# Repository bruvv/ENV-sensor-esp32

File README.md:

# ENV Sensor ESP32

Custom ESP32-S3 environmental sensor PCB designed for use with ESPHome and Home Assistant.

The board combines several environmental sensors, a 128×128 OLED display and an HLK-LD2450 mmWave presence sensor on a compact custom PCB.

## Features

- ESP32-S3 DevKitC N16R8
- Sensirion SCD30 CO₂ sensor
- Sensirion SEN55 environmental sensor
- MS5611 barometric pressure sensor
- BH1750 ambient light sensor
- ZJY-M150 128×128 OLED with SSD1327 controller
- HLK-LD2450 mmWave presence sensor
- Shared I²C bus for environmental sensors
- SPI interface for the OLED display
- Hardware UART for the LD2450
- 5 V and 3.3 V power rails
- 4-layer PCB
- 55 × 70 mm board
- Designed in KiCad 10

## Sensors

| Component | Function | Supply | Interface |
| --- | --- | ---: | --- |
| ESP32-S3 DevKitC N16R8 | Main controller, Wi-Fi and Bluetooth | 5 V | - |
| Sensirion SCD30 | CO₂, temperature and humidity | 5 V | I²C |
| Sensirion SEN55 | PM1.0, PM2.5, PM4, PM10, VOC, NOx, temperature and humidity | 5 V | I²C |
| MS5611 | Barometric pressure | 3.3 V | I²C |
| BH1750 | Ambient light | 3.3 V | I²C |
| ZJY-M150 / SSD1327 | 128×128 OLED display | 3.3 V | SPI |
| HLK-LD2450 | mmWave presence and multi-target tracking | 5 V | UART |

## ESP32 Pin Mapping

### I²C

| Signal | ESP32-S3 |
| --- | --- |
| SDA | GPIO8 |
| SCL | GPIO9 |

The environmental sensors share the I²C bus.

| Sensor | I²C address |
| --- | ---: |
| SCD30 | `0x61` |
| SEN55 | `0x69` |
| BH1750 | `0x23` |
| MS5611 | `0x77` |

The PCB contains 4.7 kΩ pull-up resistors for SDA and SCL.

## SSD1327 OLED

The ZJY-M150 OLED is operated in 4-wire SPI mode.

| OLED signal | ESP32-S3 |
| --- | --- |
| CS | GPIO10 |
| MOSI / SDA | GPIO11 |
| CLK / SCL | GPIO12 |
| DC | GPIO13 |
| RESET | GPIO14 |

## HLK-LD2450

The LD2450 uses a dedicated hardware UART.

| Signal | ESP32-S3 |
| --- | --- |
| LD2450 RX | GPIO17 / ESP32 TX |
| LD2450 TX | GPIO18 / ESP32 RX |

UART configuration:

- Baud rate: `256000`
- Data bits: `8`
- Parity: none
- Stop bits: `1`

## PCB

The current PCB revision is designed in KiCad 10.

| Property | Value |
| --- | --- |
| Dimensions | 55 × 70 mm |
| Copper layers | 4 |
| Top copper | `F.Cu` |
| Inner layer 1 | `In1.Cu` |
| Inner layer 2 | `In2.Cu` |
| Bottom copper | `B.Cu` |

The repository contains the KiCad project files as well as production Gerber and drill files.

## LD2450 Connector

The HLK-LD2450 is connected through an 8-pin dual-row SMD female socket.

Required connector specification:

| Property | Requirement |
| --- | --- |
| Type | Female PCB socket |
| Contacts | 8 |
| Rows | 2 × 4 |
| Pitch | 2.00 mm |
| Mounting | SMD / SMT |
| Orientation | Straight |

A suitable branded connector is:

**Würth Elektronik 62100821821**

- 2 × 4
- 8 contacts
- 2.00 mm pitch
- Female
- SMD

For generic alternatives, search for:

`2.0mm 2x4 8 pin female SMD header`

## SEN55 Connection

The SEN55 is mounted away from the main PCB to keep its airflow unobstructed.

The connection provides:

| Signal |
| --- |
| 5 V |
| GND |
| SDA |
| SCL |
| GND / SEL |

## Bill of Materials

| Qty | Component | Notes |
| ---: | --- | --- |
| 1 | ESP32-S3 DevKitC N16R8 | ESP32-S3-WROOM based |
| 1 | Sensirion SCD30 | CO₂ sensor |
| 1 | Sensirion SEN55 | Environmental and particulate sensor |
| 1 | MS5611 module | Pressure sensor |
| 1 | BH1750 module | Ambient light sensor |
| 1 | ZJY-M150 128×128 OLED | SSD1327 controller, 7-pin |
| 1 | HLK-LD2450 | mmWave presence sensor |
| 1 | 2×4 2.00 mm female SMD socket | LD2450 connector |
| 2 | 4.7 kΩ resistor | I²C pull-ups |

## Design Considerations

### SCD30

The SCD30 should be kept away from heat sources and strong direct airflow that could influence its temperature and CO₂ measurements.

Datasheet:  
https://sensirion.com/media/documents/4EAF6AF8/61652C3C/Sensirion_CO2_Sensors_SCD30_Datasheet.pdf

### SEN55

The SEN55 requires unobstructed airflow through its inlet and outlet.

For best performance:

- Keep the inlet and outlet separated.
- Avoid recirculating exhaust air into the inlet.
- Keep the sensor away from heat sources.
- Orient the sensor so dust cannot easily accumulate inside.
- Keep the fan inlet and exhaust unobstructed.

Datasheet:  
https://sensirion.com/media/documents/6791EFA0/62A1F68F/Sensirion_Datasheet_Environmental_Node_SEN5x.pdf

### MS5611

Keep the pressure sensor away from the ESP32 voltage regulator and other heat-producing components.

Datasheet:  
https://www.te.com/commerce/DocumentDelivery/DDEController?Action=showdoc&DocId=Data+Sheet%7FMS5611-01BA03%7FB3%7Fpdf%7FEnglish%7FENG_DS_MS5611-01BA03_B3.pdf%7FCAT-BLPS0036

### BH1750

The BH1750 needs a clear optical path to the room.

Avoid placing it behind opaque enclosure material or in the shadow of other components.

Datasheet:  
https://components101.com/sites/default/files/component_datasheet/BH1750.pdf

### SSD1327 OLED

The display is a ZJY-M150 1.5-inch 128×128 OLED using an SSD1327 controller.

The PCB uses SPI for the display.

SSD1327 datasheet:  
https://www.waveshare.com/w/upload/a/ac/SSD1327-datasheet.pdf

### HLK-LD2450

The LD2450 provides mmWave presence detection and multi-target position tracking.

Placement and enclosure design can significantly affect radar performance.

Recommendations:

- Face the radar toward the room.
- Avoid metal directly in front of the antenna.
- Keep sufficient clearance around the antenna area.
- Avoid placing large copper areas or metal parts directly in the radar field of view.

## Repository Structure

`envsensor/`  
KiCad schematic, PCB project and project-specific libraries.

`gerber/`  
Production Gerber and drill files.

`datasheet/`  
Component documentation.

`docs/`  
Hardware design and implementation documentation.

`README.md`  
Project documentation.

## Manufacturing

The `gerber/` directory contains the generated PCB production files, including:

- `F.Cu`
- `In1.Cu`
- `In2.Cu`
- `B.Cu`
- `F.Mask`
- `B.Mask`
- `F.Paste`
- `B.Paste`
- `F.Silkscreen`
- `B.Silkscreen`
- `Edge.Cuts`
- PTH drill file
- NPTH drill file

The repository also contains `gerber/gerber.zip`, which can be uploaded to most PCB manufacturers.

Always verify the Gerbers in the PCB manufacturer's Gerber viewer before placing an order.

## Software

The board is intended for use with ESPHome and Home Assistant.

Useful ESPHome documentation:

- SCD30: https://esphome.io/components/sensor/scd30/
- SEN5x: https://esphome.io/components/sensor/sen5x/
- BH1750: https://esphome.io/components/sensor/bh1750/
- MS5611: https://esphome.io/components/sensor/ms5611/
- SSD1327: https://esphome.io/components/display/ssd1327/
- LD2450: https://esphome.io/components/sensor/ld2450/

## License

See [LICENSE](LICENSE).

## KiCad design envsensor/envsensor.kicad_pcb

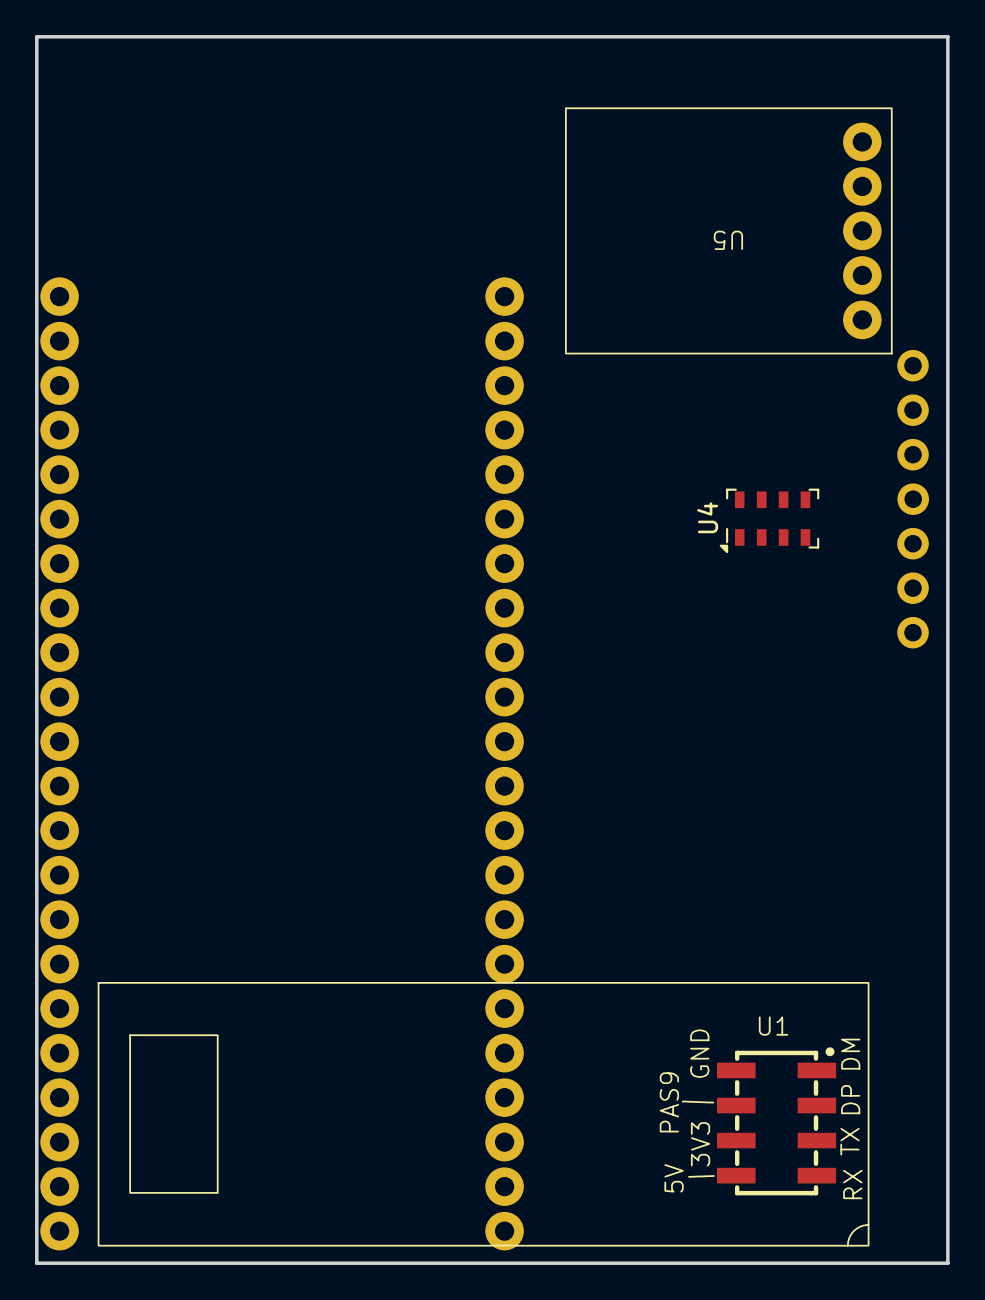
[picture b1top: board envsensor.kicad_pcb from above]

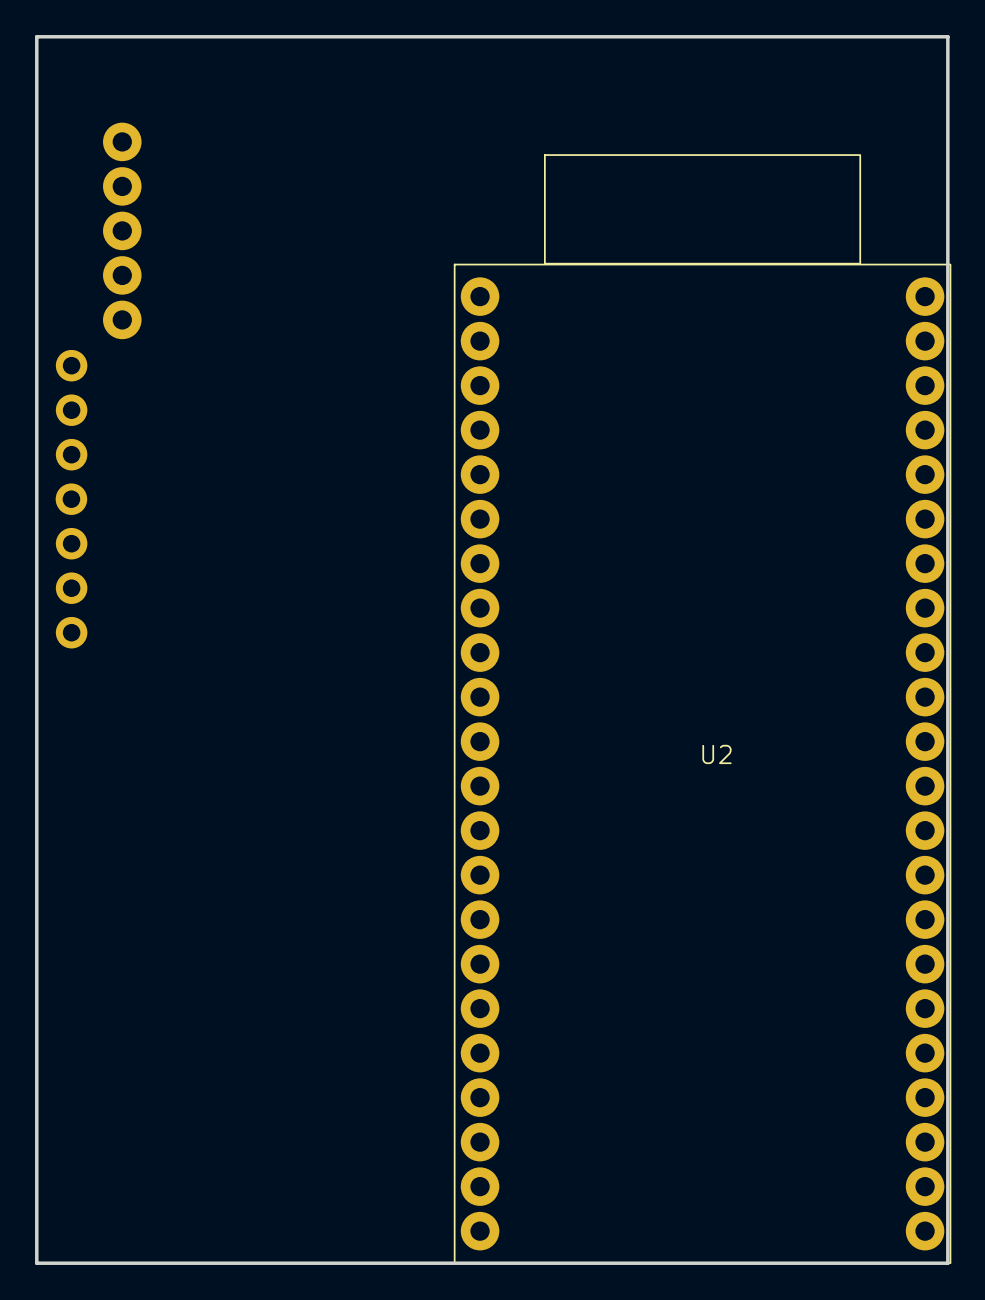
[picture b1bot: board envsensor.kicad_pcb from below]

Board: 2 copper layers, 52.0 x 70.0 mm, 5 parts (2 on the bottom side), 3 nets, no tracks yet.

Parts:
U1: LD2450; ld2450
U2: esp32-s3-wroom-1-devkit
U3: SCD30
U4: MS5611-01BA; LGA-8_3x5mm_P1.25mm
U5: BH1750

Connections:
3V3: U1.6 (3V3), U3.1 (VDD)
GND: U1.8 (GND), U3.2 (GND), U4.3 (GND)
unnamed: U4.4 (CSB), U4.5 (CSB)

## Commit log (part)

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2025-10-05 first draft
2026-01-04 Expand README with sensor considerations and guidelines
    Added considerations and guidelines for various sensors including SCD30, SEN55, and LD2450.
2026-06-13 Add submodule for ld2450 library
2026-06-13 Add new components and libraries for environmental sensor project
    - Created schematic for ESP32 WROOM 1 Devkit in envsensor.kicad_sch.
    - Added footprint library entry for LD2450 in fp-lib-table.
    - Established backup and main symbol files for BH1750 light sensor in bh1750.bak and bh1750.kicad_sym.
    - Defined module for BH1750 in BH1750-MODULE.kicad_mod with appropriate pads and silk screen markings.
    - Updated sym-lib-table to include LD2450 symbol library.
2026-06-13 docs: add env sensor hardware design
2026-06-13 docs: add KiCad implementation plan
2026-06-13 cleanup
2026-06-13 [ImgBot] Optimize images
    /envsensor/oud/lib/ld2450/screenshot.png -- 84.51kb -> 43.58kb (48.43%)
2026-06-13 added datasheets and extra information
2026-06-13 ignore stuff
2026-06-13 added 3d models
2026-06-13 added led screen
2026-06-13 noop
2026-06-13 Remove accidental temporary file
2026-06-15 final version
